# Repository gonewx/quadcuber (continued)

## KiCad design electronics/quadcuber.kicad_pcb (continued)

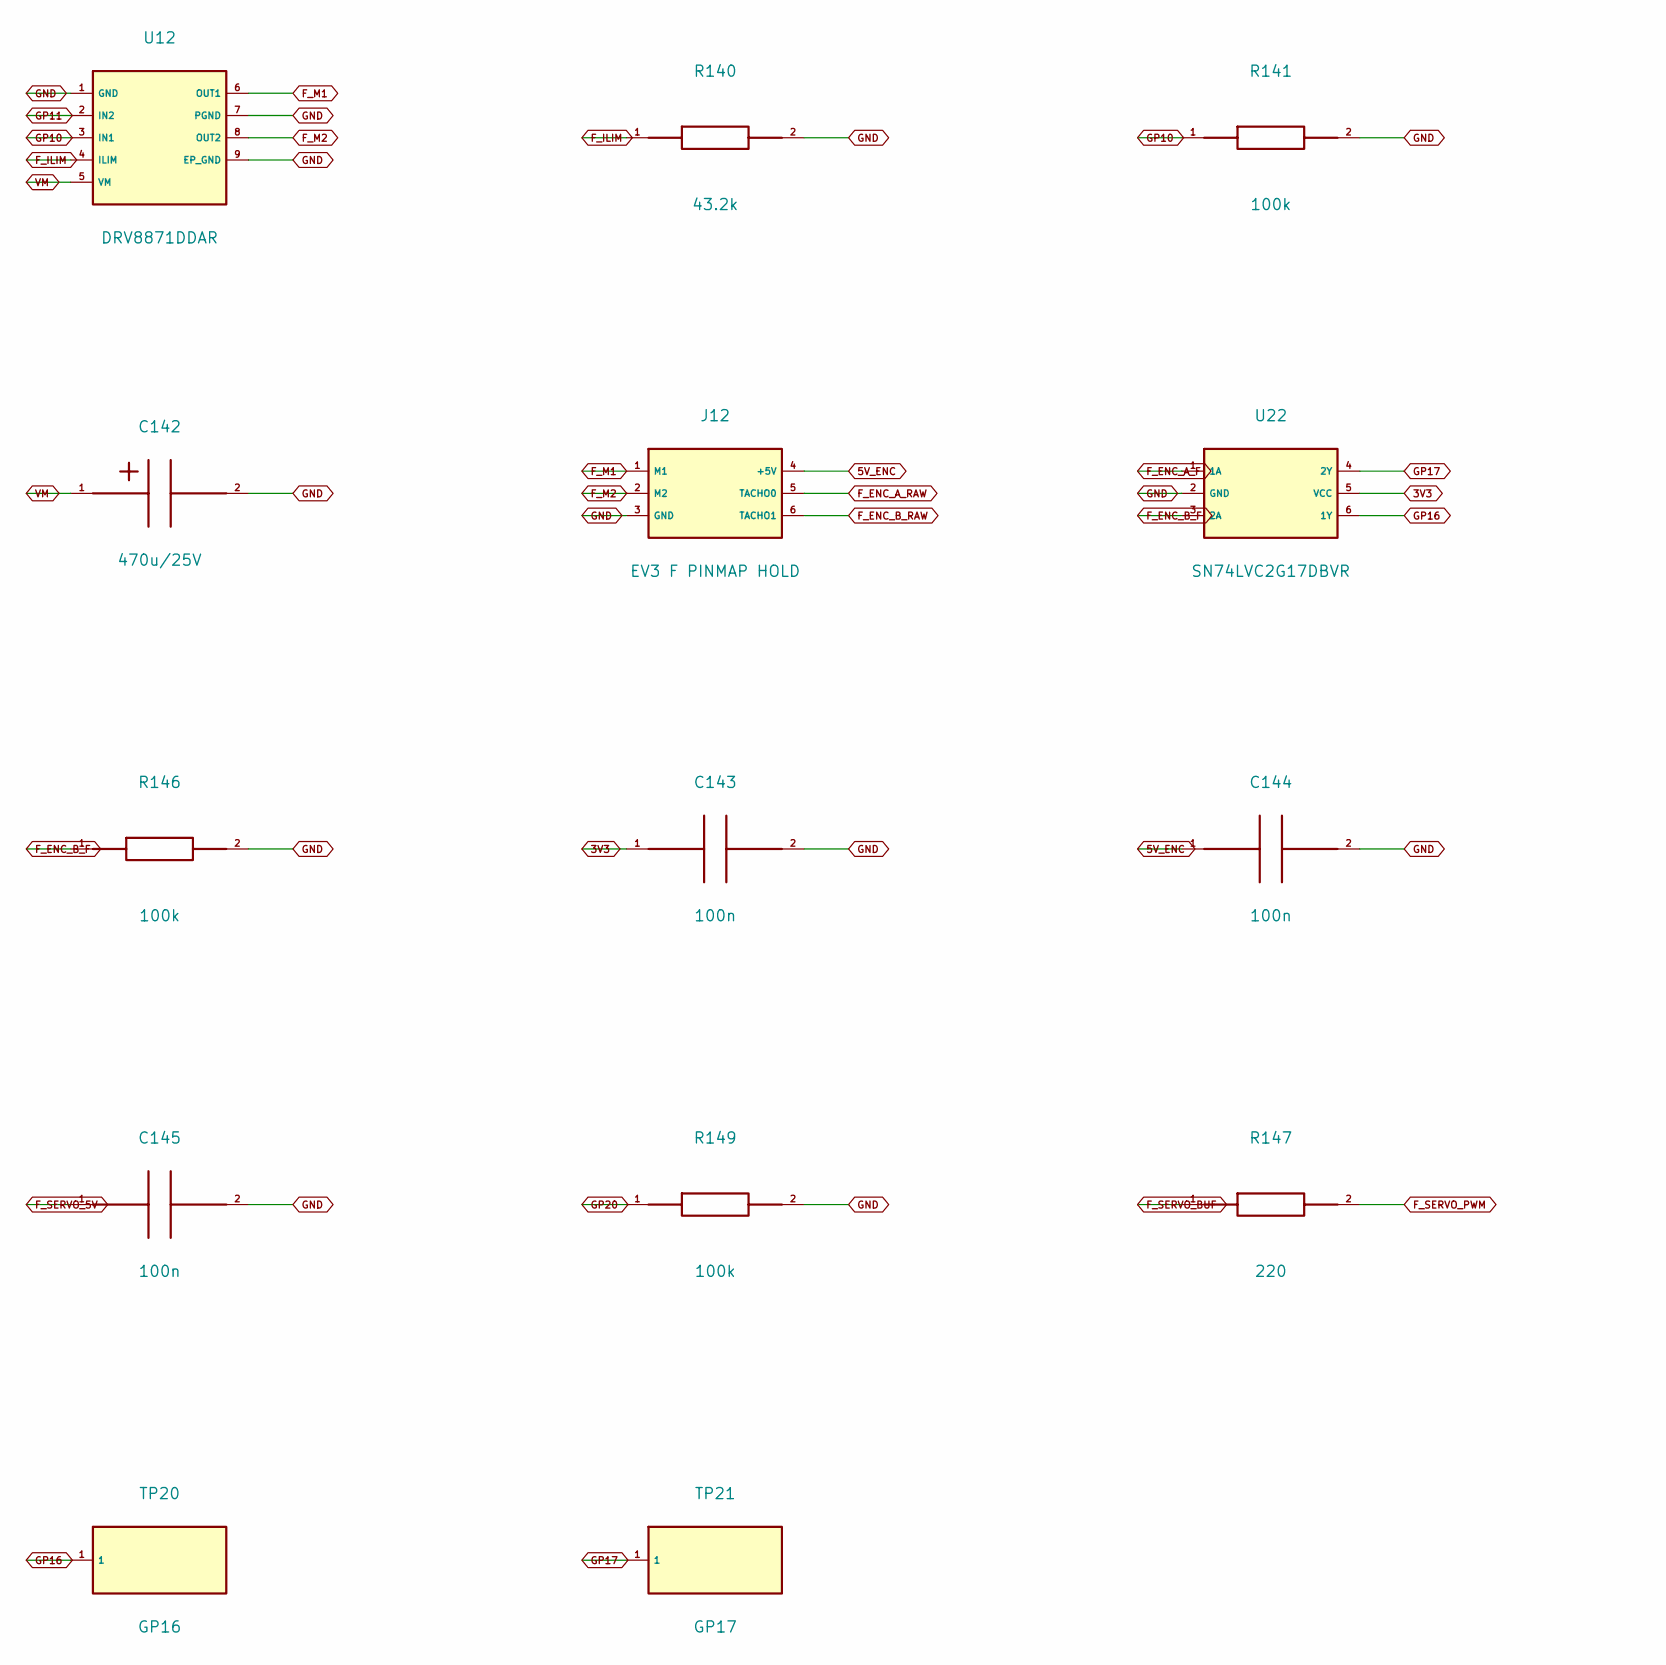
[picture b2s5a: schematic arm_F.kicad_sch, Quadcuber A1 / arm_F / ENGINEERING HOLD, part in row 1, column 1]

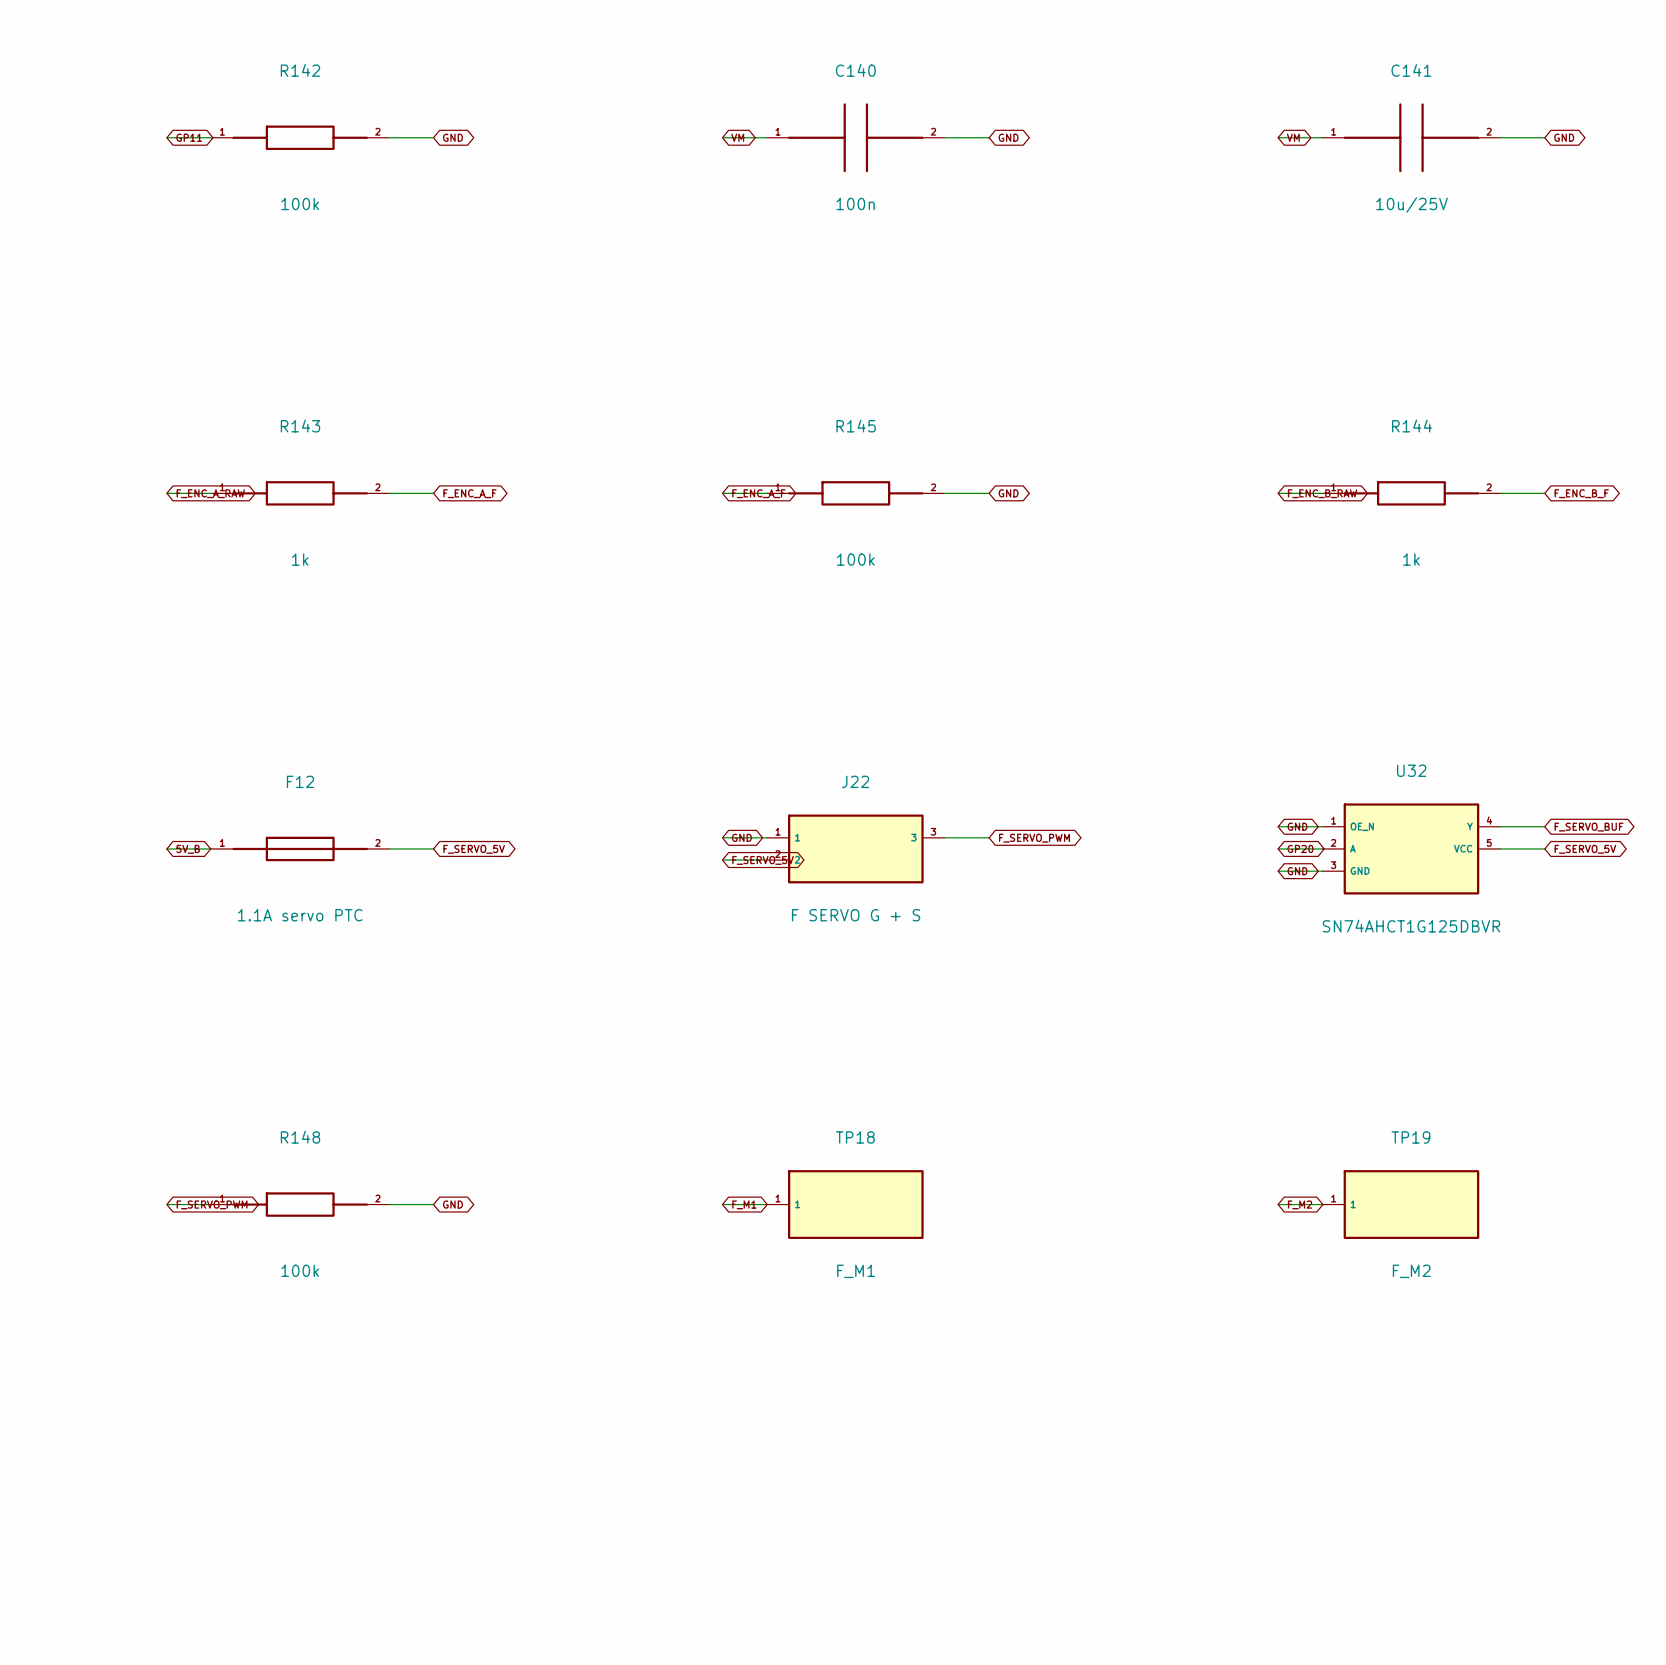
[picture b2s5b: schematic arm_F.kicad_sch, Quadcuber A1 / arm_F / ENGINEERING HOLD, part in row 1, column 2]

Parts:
C140, C143, C144, C145: 100n; C_0805_2012Metric; MPN GRM21BR71H104KA01L
C141: 10u/25V; C_1210_3225Metric; MPN GRM32DR71E106KA12L
C142: 470u/25V; CP_Radial_D10.0mm_P5.00mm; MPN EEU-FR1E471
F12: 1.1A servo PTC; Fuse_Bourns_MF_MSMF_Style2_1812; MPN MF-MSMF110/16X-2
J12: EV3 F PINMAP HOLD; EV3_UserDrawing_PINMAP_HOLD; MPN UNCONFIRMED user drawing
J22: F SERVO G + S; PinHeader_1x03_P2.54mm_Vertical; MPN 61300311121
R140: 43.2k; R_0603_1608Metric; MPN RC0603FR-0743K2L
R141, R142, R145, R146, R148, R149: 100k; R_0603_1608Metric; MPN RC0603FR-07100KL
R143, R144: 1k; R_0603_1608Metric; MPN RC0603FR-071KL
R147: 220; R_0603_1608Metric; MPN RC0603FR-07220RL
TP18: F_M1; TestPoint_Pad_D1.5mm; MPN N/A PCB copper
TP19: F_M2; TestPoint_Pad_D1.5mm; MPN N/A PCB copper
TP20: GP16; TestPoint_Pad_D1.5mm; MPN N/A PCB copper
TP21: GP17; TestPoint_Pad_D1.5mm; MPN N/A PCB copper
U12: DRV8871DDAR; Texas_HTSOP-8-1EP_3.9x4.9mm_P1.27mm_EP2.95x4.9mm_Mask2.4x3.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; MPN DRV8871DDAR
U22: SN74LVC2G17DBVR; SOT-23-6; MPN SN74LVC2G17DBVR
U32: SN74AHCT1G125DBVR; SOT-23-5; MPN SN74AHCT1G125DBVR

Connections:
3V3: C143.1, U22.5 (VCC); also elsewhere on the board
5V_B: F12.1; also elsewhere on the board
5V_ENC: C144.1, J12.4 (+5V); also elsewhere on the board
F_ENC_A_F: R143.2, R145.1, U22.1 (1A)
F_ENC_A_RAW: J12.5 (TACHO0), R143.1
F_ENC_B_F: R144.2, R146.1, U22.3 (2A)
F_ENC_B_RAW: J12.6 (TACHO1), R144.1
F_ILIM: R140.1, U12.4 (ILIM)
F_M1: J12.1 (M1), TP18.1, U12.6 (OUT1)
F_M2: J12.2 (M2), TP19.1, U12.8 (OUT2)
F_SERVO_5V: C145.1, F12.2, J22.2, U32.5 (VCC)
F_SERVO_BUF: R147.1, U32.4 (Y)
F_SERVO_PWM: J22.3, R147.2, R148.1
GND: C140.2, C141.2, C142.2 (-), C143.2, C144.2, C145.2, J12.3 (GND), J22.1, R140.2, R141.2, R142.2, R145.2, R146.2, R148.2, R149.2, U12.1 (GND), U12.7 (PGND), U12.9 (EP_GND), U22.2 (GND), U32.1 (OE_N), U32.3 (GND); also elsewhere on the board
GP10: R141.1, U12.3 (IN1); also elsewhere on the board
GP11: R142.1, U12.2 (IN2); also elsewhere on the board
GP16: TP20.1, U22.6 (1Y); also elsewhere on the board
GP17: TP21.1, U22.4 (2Y); also elsewhere on the board
GP20: R149.1, U32.2 (A); also elsewhere on the board
VM: C140.1, C141.1, C142.1 (+), U12.5 (VM); also elsewhere on the board

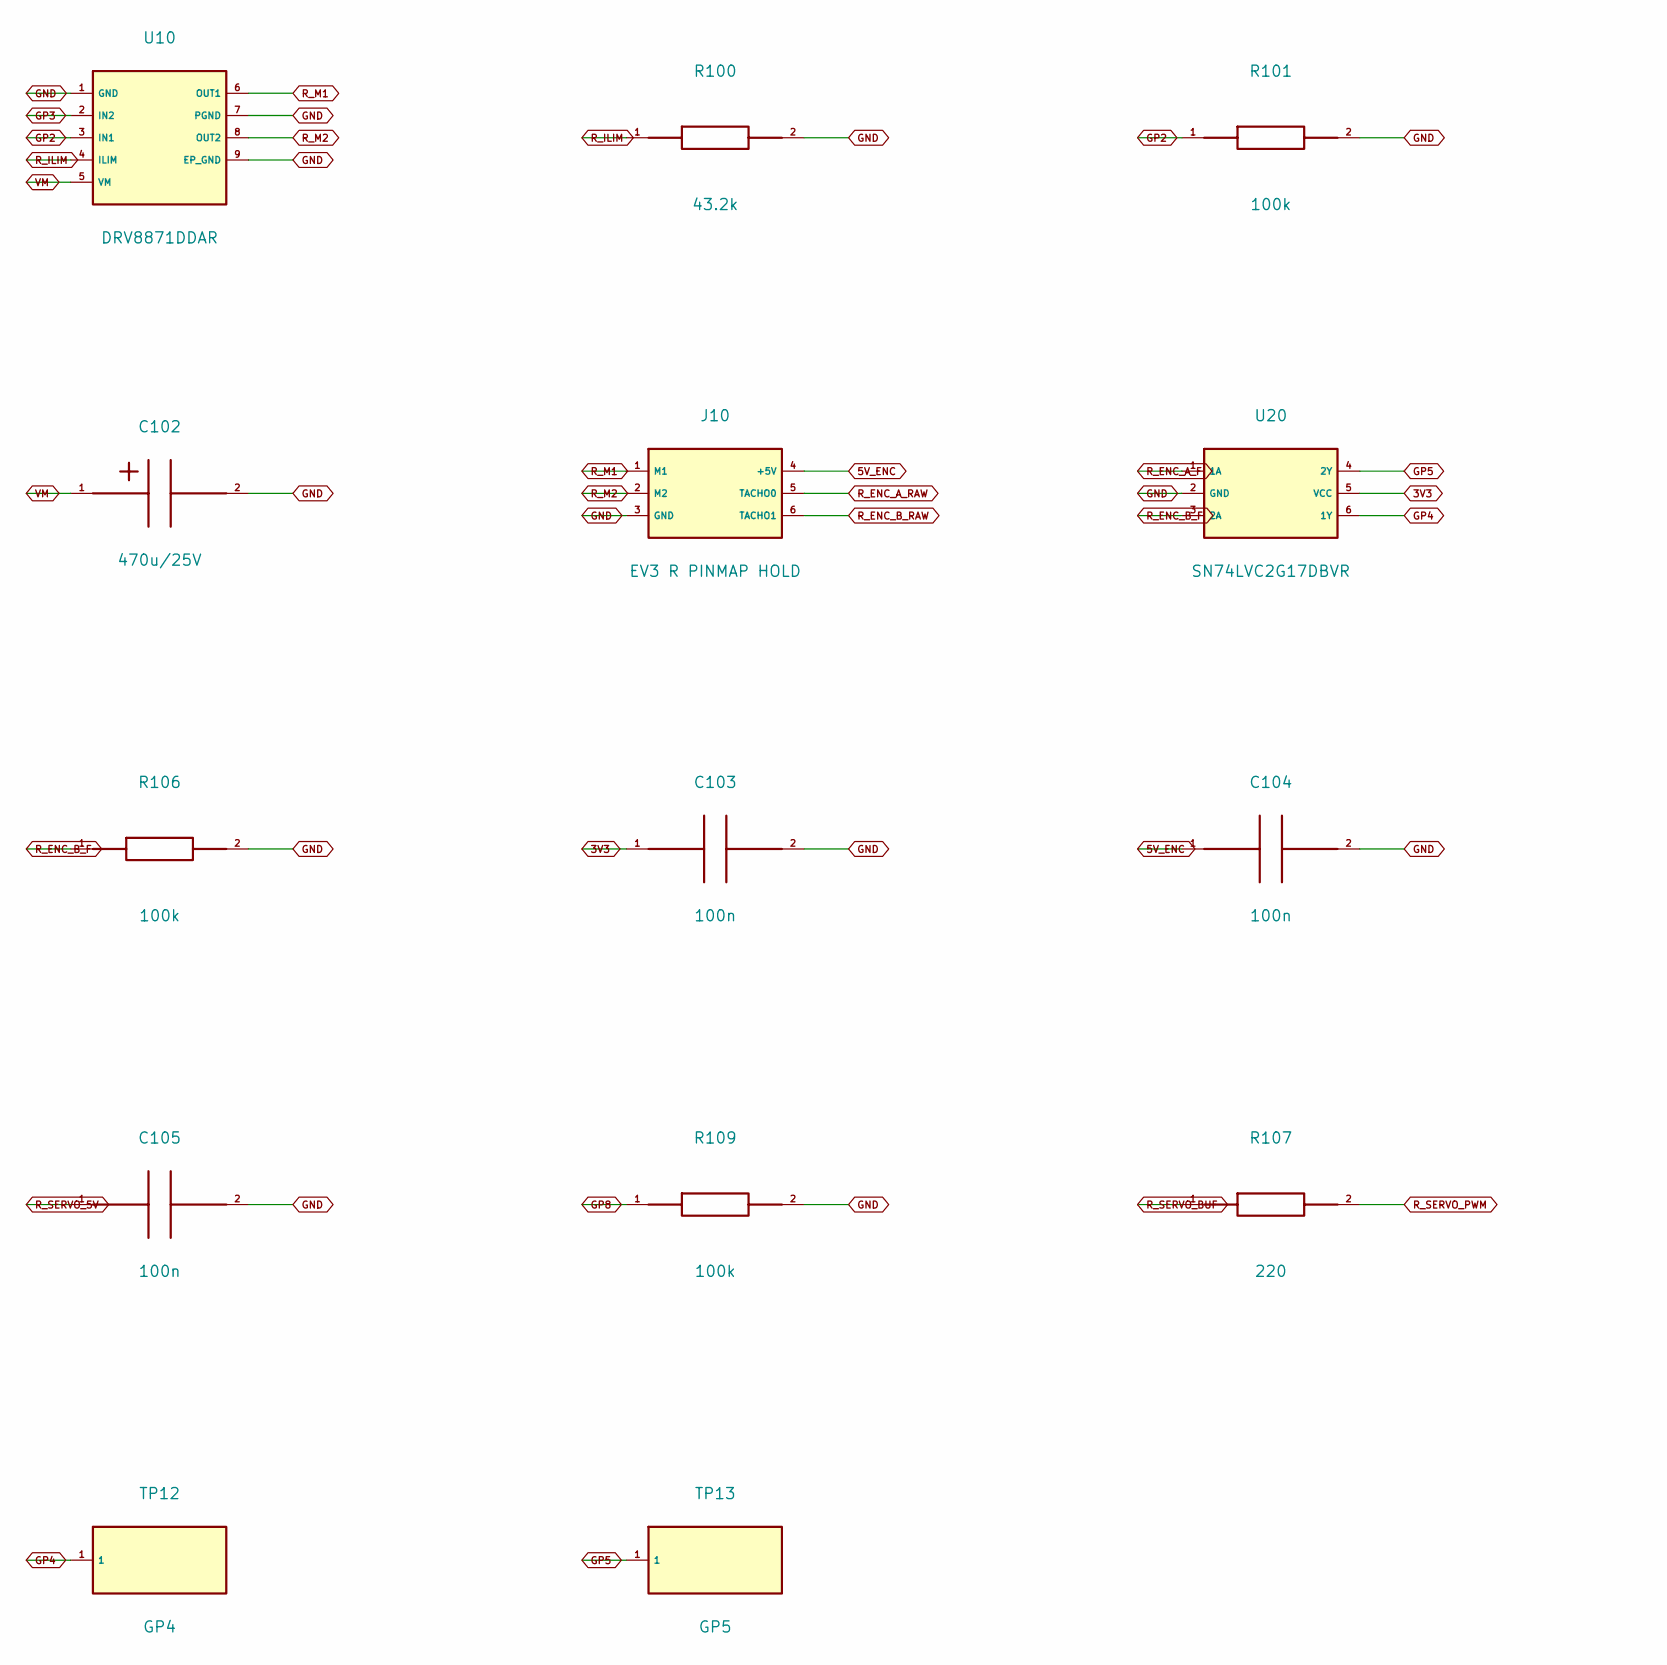
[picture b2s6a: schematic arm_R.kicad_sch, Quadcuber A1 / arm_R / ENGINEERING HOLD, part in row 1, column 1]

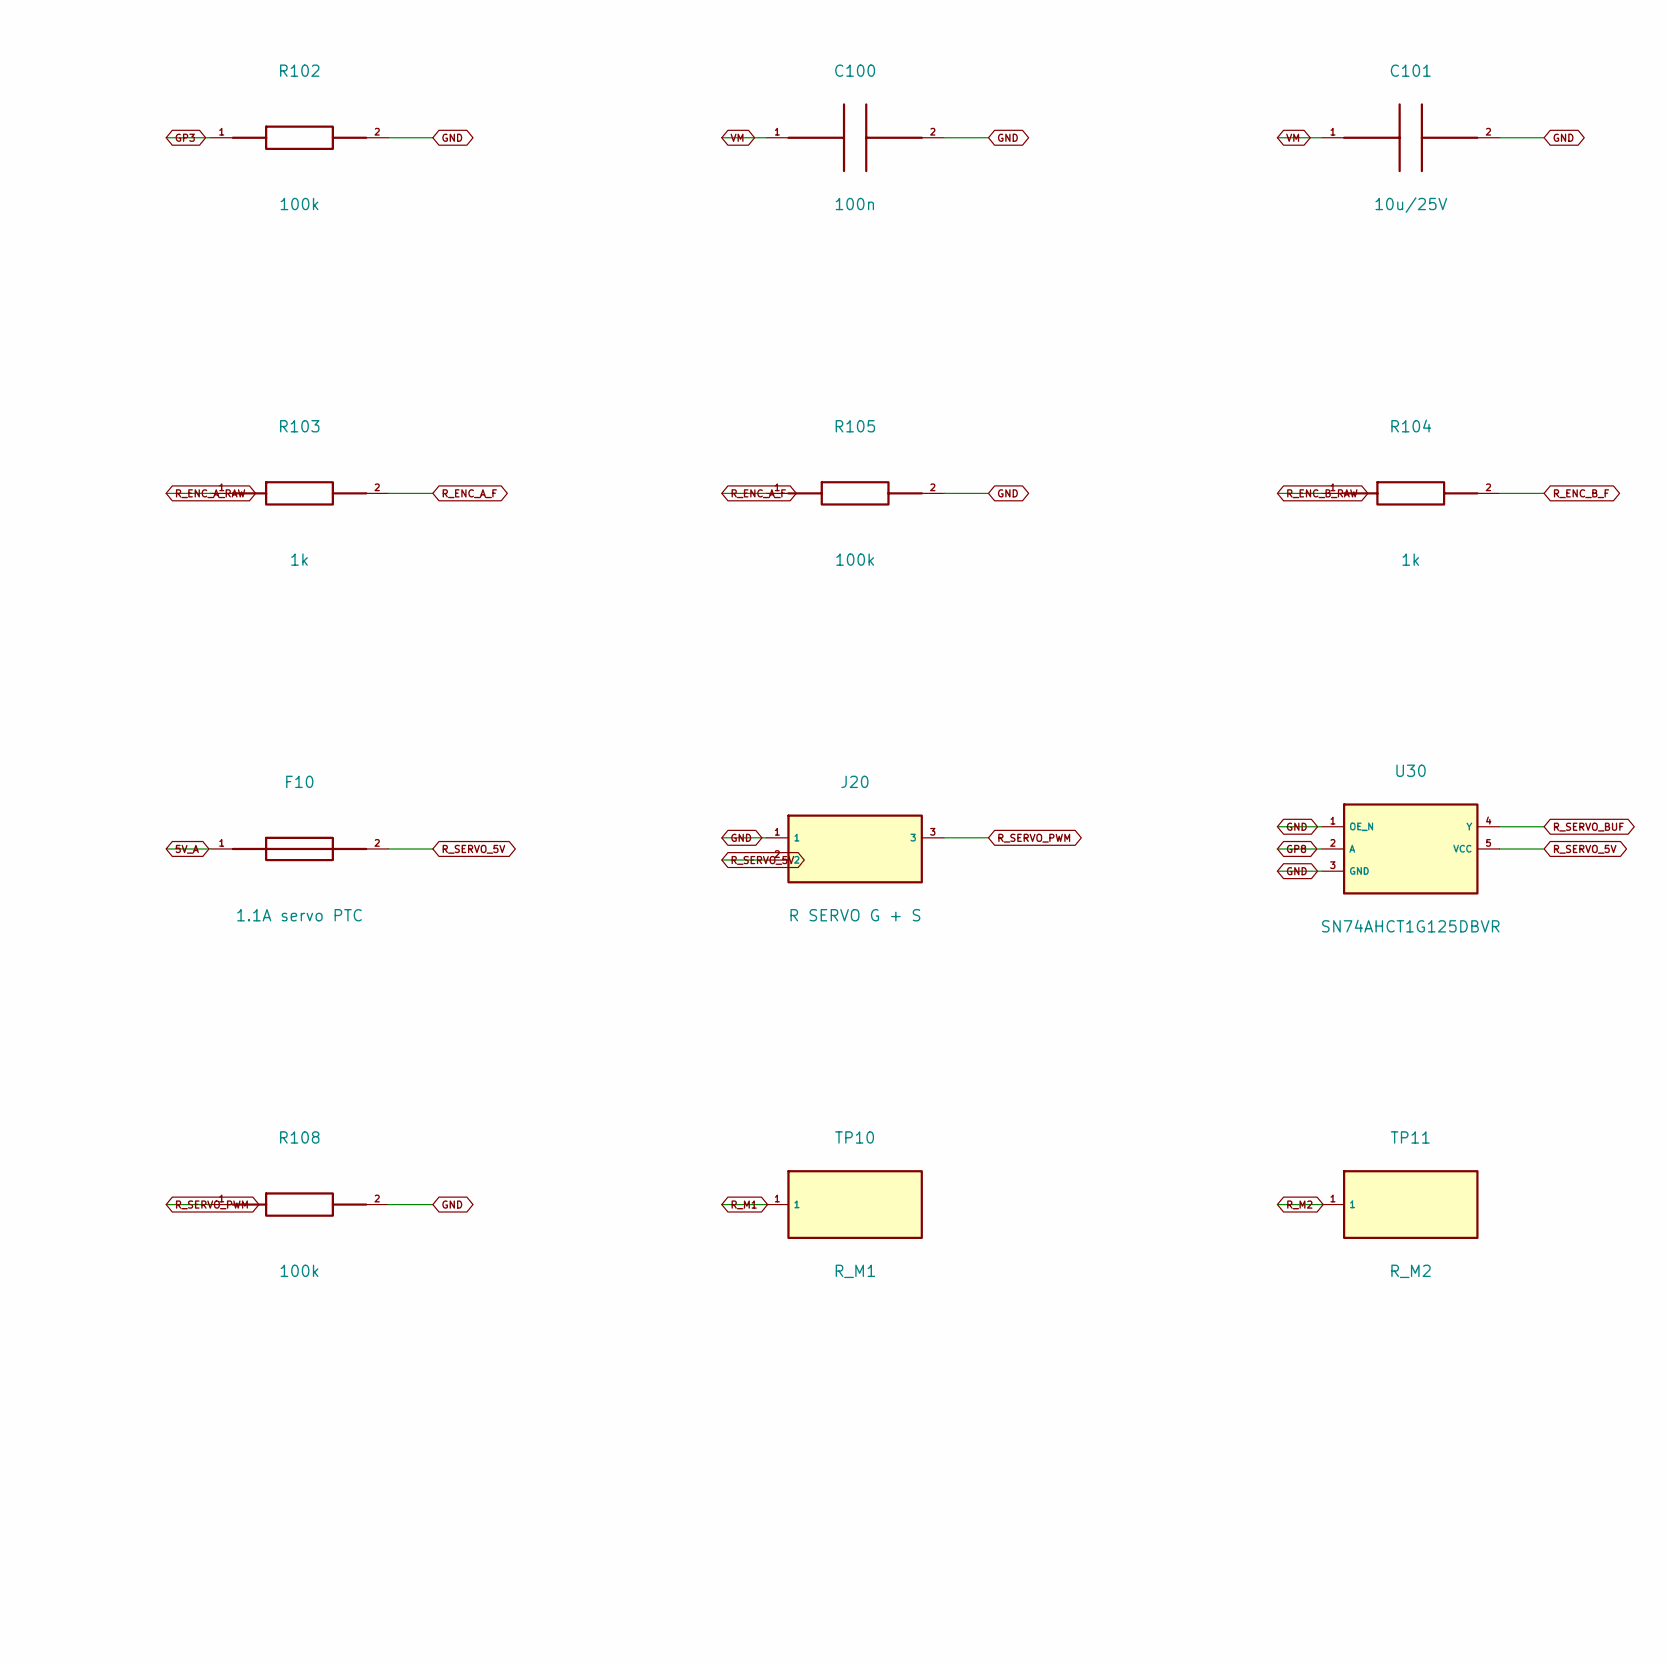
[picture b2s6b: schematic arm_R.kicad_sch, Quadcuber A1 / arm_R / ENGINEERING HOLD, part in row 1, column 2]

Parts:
C100, C103, C104, C105: 100n; C_0805_2012Metric; MPN GRM21BR71H104KA01L
C101: 10u/25V; C_1210_3225Metric; MPN GRM32DR71E106KA12L
C102: 470u/25V; CP_Radial_D10.0mm_P5.00mm; MPN EEU-FR1E471
F10: 1.1A servo PTC; Fuse_Bourns_MF_MSMF_Style2_1812; MPN MF-MSMF110/16X-2
J10: EV3 R PINMAP HOLD; EV3_UserDrawing_PINMAP_HOLD; MPN UNCONFIRMED user drawing
J20: R SERVO G + S; PinHeader_1x03_P2.54mm_Vertical; MPN 61300311121
R100: 43.2k; R_0603_1608Metric; MPN RC0603FR-0743K2L
R101, R102, R105, R106, R108, R109: 100k; R_0603_1608Metric; MPN RC0603FR-07100KL
R103, R104: 1k; R_0603_1608Metric; MPN RC0603FR-071KL
R107: 220; R_0603_1608Metric; MPN RC0603FR-07220RL
TP10: R_M1; TestPoint_Pad_D1.5mm; MPN N/A PCB copper
TP11: R_M2; TestPoint_Pad_D1.5mm; MPN N/A PCB copper
TP12: GP4; TestPoint_Pad_D1.5mm; MPN N/A PCB copper
TP13: GP5; TestPoint_Pad_D1.5mm; MPN N/A PCB copper
U10: DRV8871DDAR; Texas_HTSOP-8-1EP_3.9x4.9mm_P1.27mm_EP2.95x4.9mm_Mask2.4x3.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; MPN DRV8871DDAR
U20: SN74LVC2G17DBVR; SOT-23-6; MPN SN74LVC2G17DBVR
U30: SN74AHCT1G125DBVR; SOT-23-5; MPN SN74AHCT1G125DBVR

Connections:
3V3: C103.1, U20.5 (VCC); also elsewhere on the board
5V_A: F10.1; also elsewhere on the board
5V_ENC: C104.1, J10.4 (+5V); also elsewhere on the board
GND: C100.2, C101.2, C102.2 (-), C103.2, C104.2, C105.2, J10.3 (GND), J20.1, R100.2, R101.2, R102.2, R105.2, R106.2, R108.2, R109.2, U10.1 (GND), U10.7 (PGND), U10.9 (EP_GND), U20.2 (GND), U30.1 (OE_N), U30.3 (GND); also elsewhere on the board
GP2: R101.1, U10.3 (IN1); also elsewhere on the board
GP3: R102.1, U10.2 (IN2); also elsewhere on the board
GP4: TP12.1, U20.6 (1Y); also elsewhere on the board
GP5: TP13.1, U20.4 (2Y); also elsewhere on the board
GP8: R109.1, U30.2 (A); also elsewhere on the board
R_ENC_A_F: R103.2, R105.1, U20.1 (1A)
R_ENC_A_RAW: J10.5 (TACHO0), R103.1
R_ENC_B_F: R104.2, R106.1, U20.3 (2A)
R_ENC_B_RAW: J10.6 (TACHO1), R104.1
R_ILIM: R100.1, U10.4 (ILIM)
R_M1: J10.1 (M1), TP10.1, U10.6 (OUT1)
R_M2: J10.2 (M2), TP11.1, U10.8 (OUT2)
R_SERVO_5V: C105.1, F10.2, J20.2, U30.5 (VCC)
R_SERVO_BUF: R107.1, U30.4 (Y)
R_SERVO_PWM: J20.3, R107.2, R108.1
VM: C100.1, C101.1, C102.1 (+), U10.5 (VM); also elsewhere on the board

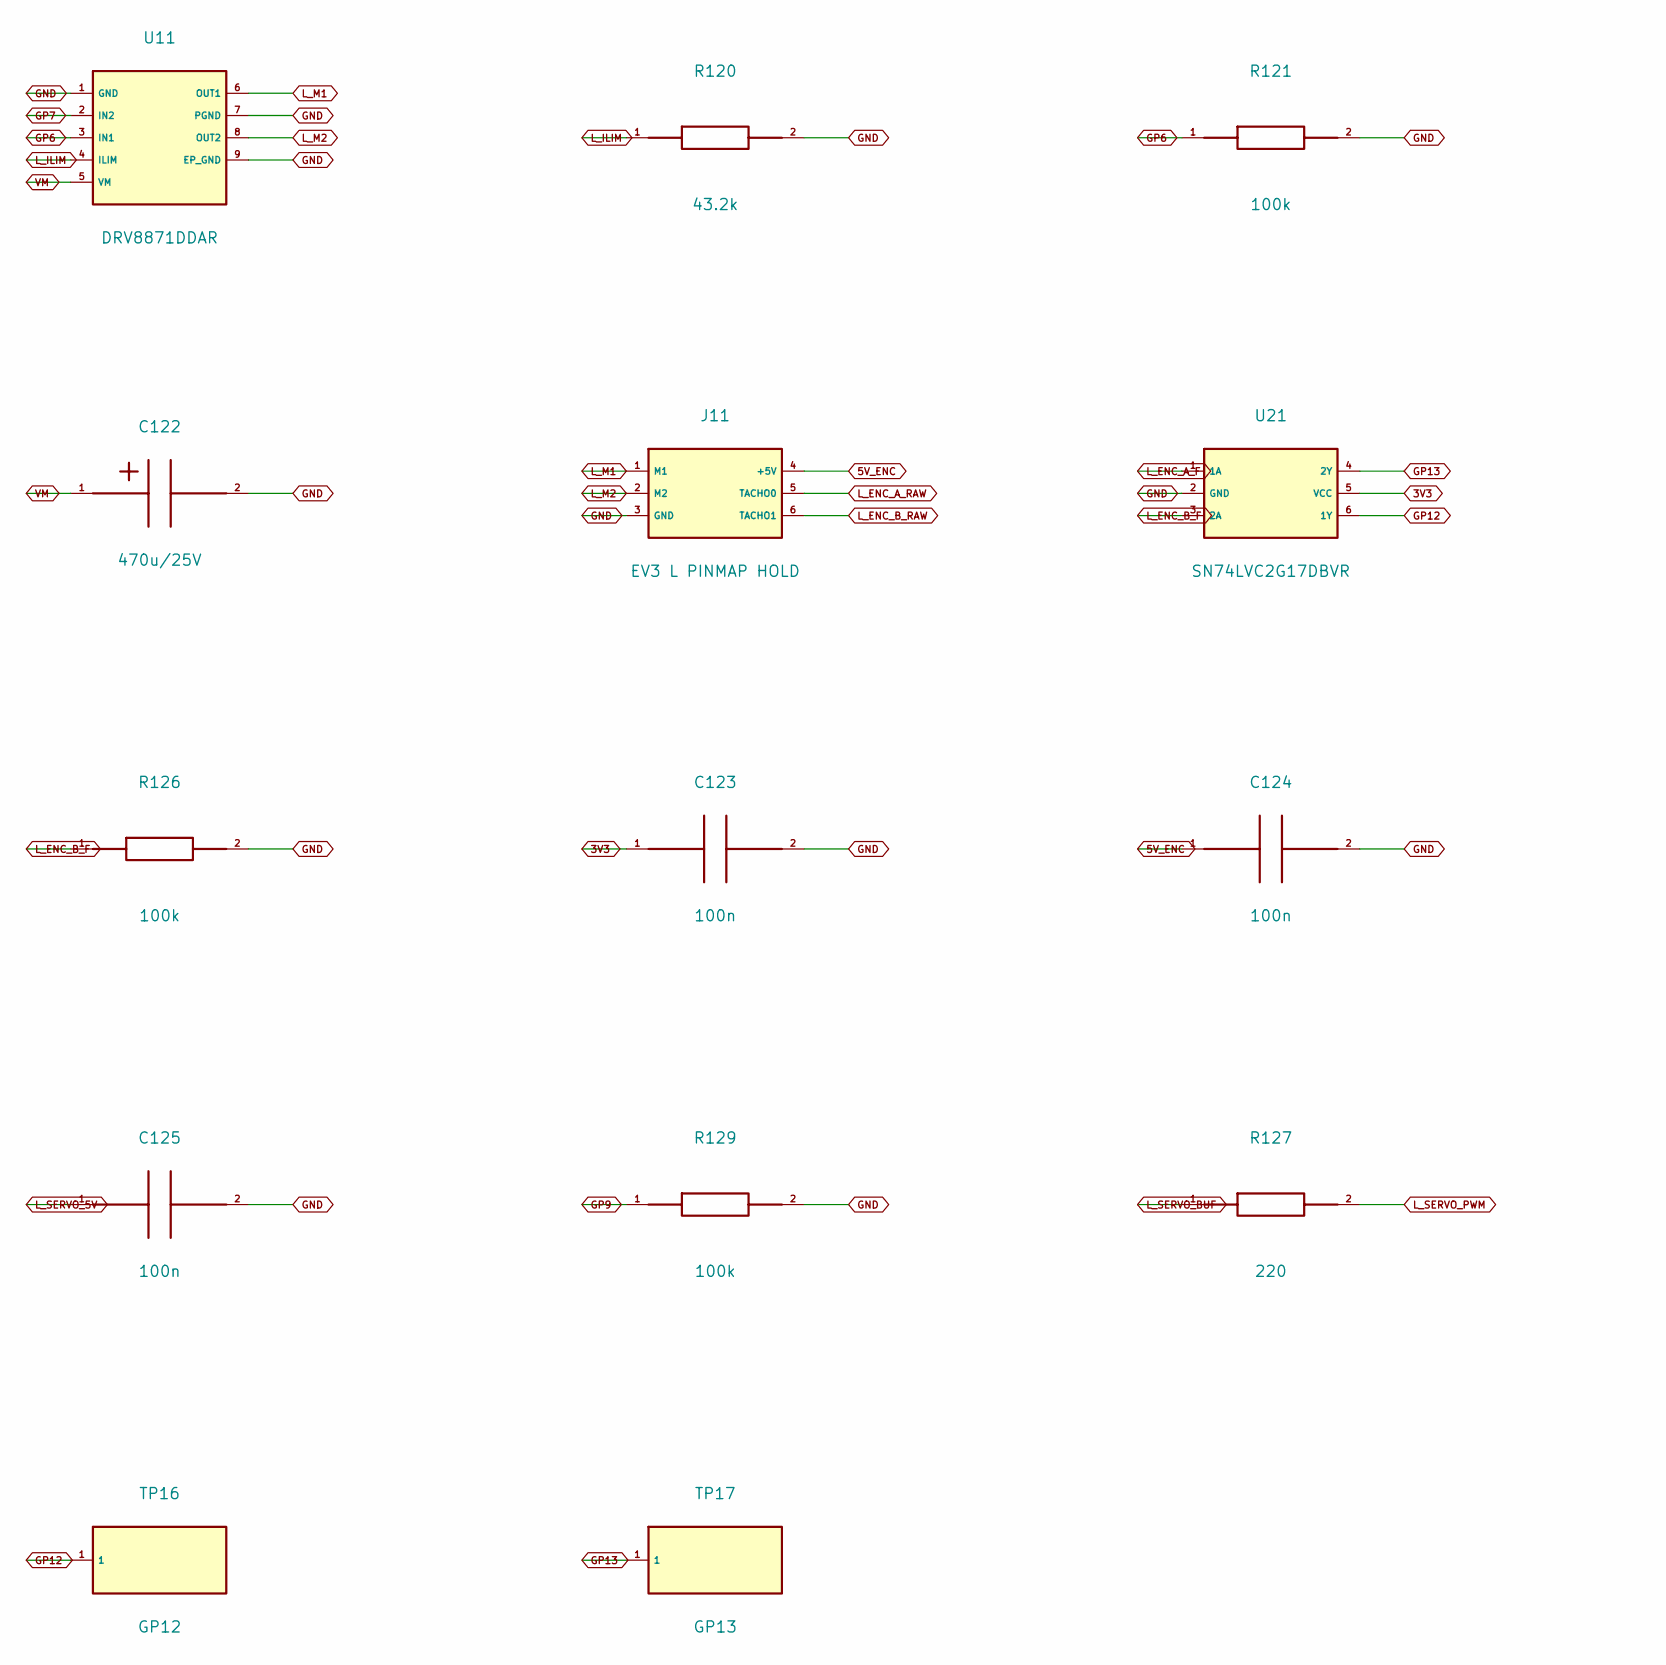
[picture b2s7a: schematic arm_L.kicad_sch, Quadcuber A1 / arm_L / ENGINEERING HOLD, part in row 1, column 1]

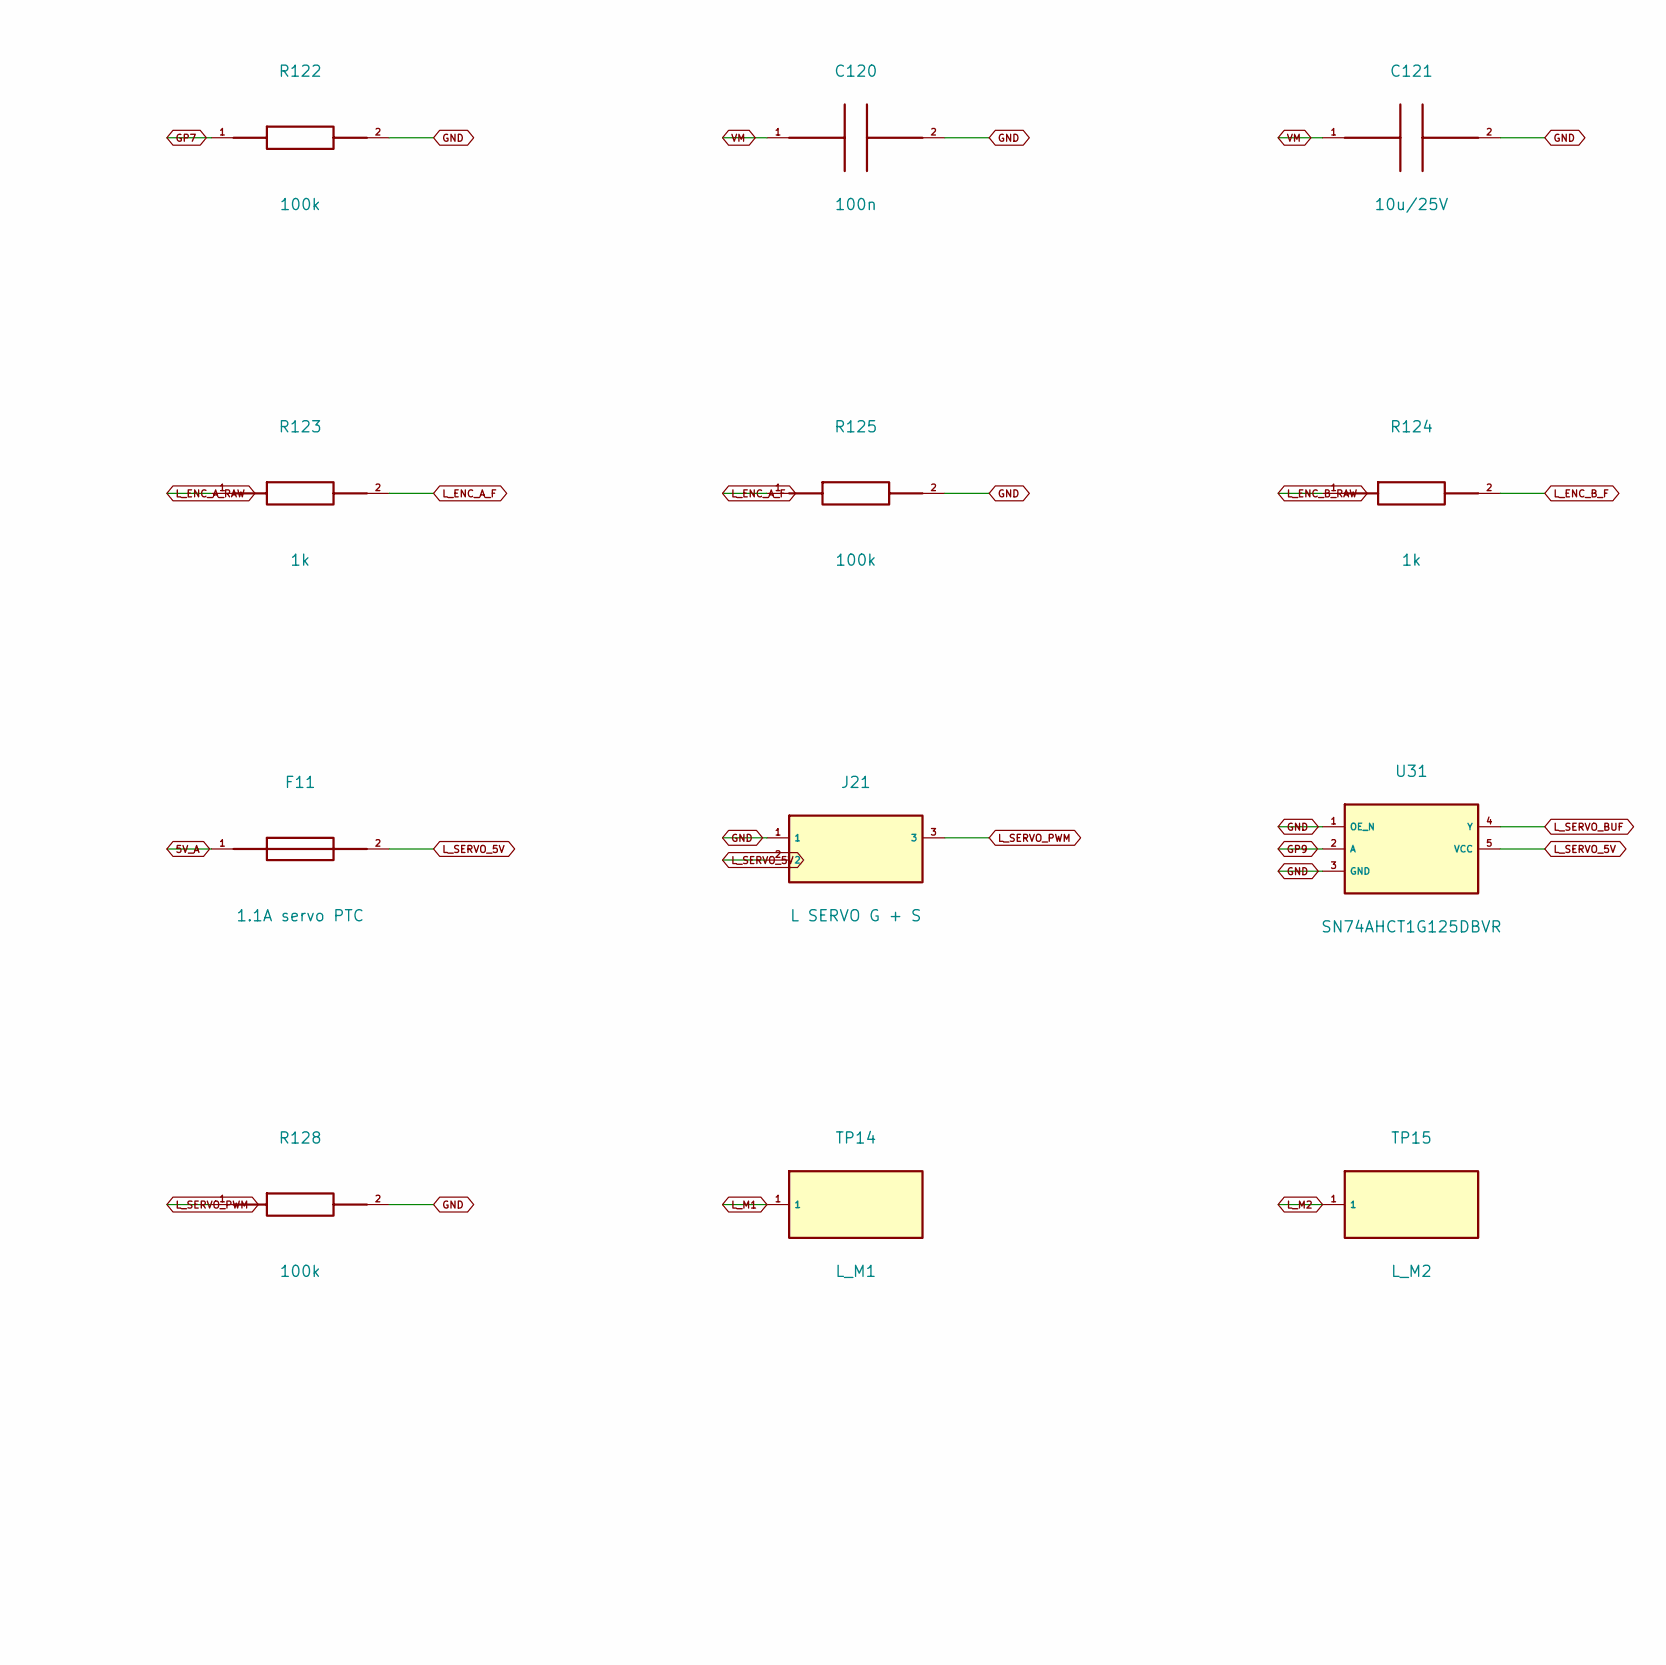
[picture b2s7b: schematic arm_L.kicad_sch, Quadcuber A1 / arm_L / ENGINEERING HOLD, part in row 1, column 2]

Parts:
C120, C123, C124, C125: 100n; C_0805_2012Metric; MPN GRM21BR71H104KA01L
C121: 10u/25V; C_1210_3225Metric; MPN GRM32DR71E106KA12L
C122: 470u/25V; CP_Radial_D10.0mm_P5.00mm; MPN EEU-FR1E471
F11: 1.1A servo PTC; Fuse_Bourns_MF_MSMF_Style2_1812; MPN MF-MSMF110/16X-2
J11: EV3 L PINMAP HOLD; EV3_UserDrawing_PINMAP_HOLD; MPN UNCONFIRMED user drawing
J21: L SERVO G + S; PinHeader_1x03_P2.54mm_Vertical; MPN 61300311121
R120: 43.2k; R_0603_1608Metric; MPN RC0603FR-0743K2L
R121, R122, R125, R126, R128, R129: 100k; R_0603_1608Metric; MPN RC0603FR-07100KL
R123, R124: 1k; R_0603_1608Metric; MPN RC0603FR-071KL
R127: 220; R_0603_1608Metric; MPN RC0603FR-07220RL
TP14: L_M1; TestPoint_Pad_D1.5mm; MPN N/A PCB copper
TP15: L_M2; TestPoint_Pad_D1.5mm; MPN N/A PCB copper
TP16: GP12; TestPoint_Pad_D1.5mm; MPN N/A PCB copper
TP17: GP13; TestPoint_Pad_D1.5mm; MPN N/A PCB copper
U11: DRV8871DDAR; Texas_HTSOP-8-1EP_3.9x4.9mm_P1.27mm_EP2.95x4.9mm_Mask2.4x3.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; MPN DRV8871DDAR
U21: SN74LVC2G17DBVR; SOT-23-6; MPN SN74LVC2G17DBVR
U31: SN74AHCT1G125DBVR; SOT-23-5; MPN SN74AHCT1G125DBVR

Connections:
3V3: C123.1, U21.5 (VCC); also elsewhere on the board
5V_A: F11.1; also elsewhere on the board
5V_ENC: C124.1, J11.4 (+5V); also elsewhere on the board
GND: C120.2, C121.2, C122.2 (-), C123.2, C124.2, C125.2, J11.3 (GND), J21.1, R120.2, R121.2, R122.2, R125.2, R126.2, R128.2, R129.2, U11.1 (GND), U11.7 (PGND), U11.9 (EP_GND), U21.2 (GND), U31.1 (OE_N), U31.3 (GND); also elsewhere on the board
GP6: R121.1, U11.3 (IN1); also elsewhere on the board
GP7: R122.1, U11.2 (IN2); also elsewhere on the board
GP9: R129.1, U31.2 (A); also elsewhere on the board
GP12: TP16.1, U21.6 (1Y); also elsewhere on the board
GP13: TP17.1, U21.4 (2Y); also elsewhere on the board
L_ENC_A_F: R123.2, R125.1, U21.1 (1A)
L_ENC_A_RAW: J11.5 (TACHO0), R123.1
L_ENC_B_F: R124.2, R126.1, U21.3 (2A)
L_ENC_B_RAW: J11.6 (TACHO1), R124.1
L_ILIM: R120.1, U11.4 (ILIM)
L_M1: J11.1 (M1), TP14.1, U11.6 (OUT1)
L_M2: J11.2 (M2), TP15.1, U11.8 (OUT2)
L_SERVO_5V: C125.1, F11.2, J21.2, U31.5 (VCC)
L_SERVO_BUF: R127.1, U31.4 (Y)
L_SERVO_PWM: J21.3, R127.2, R128.1
VM: C120.1, C121.1, C122.1 (+), U11.5 (VM); also elsewhere on the board
